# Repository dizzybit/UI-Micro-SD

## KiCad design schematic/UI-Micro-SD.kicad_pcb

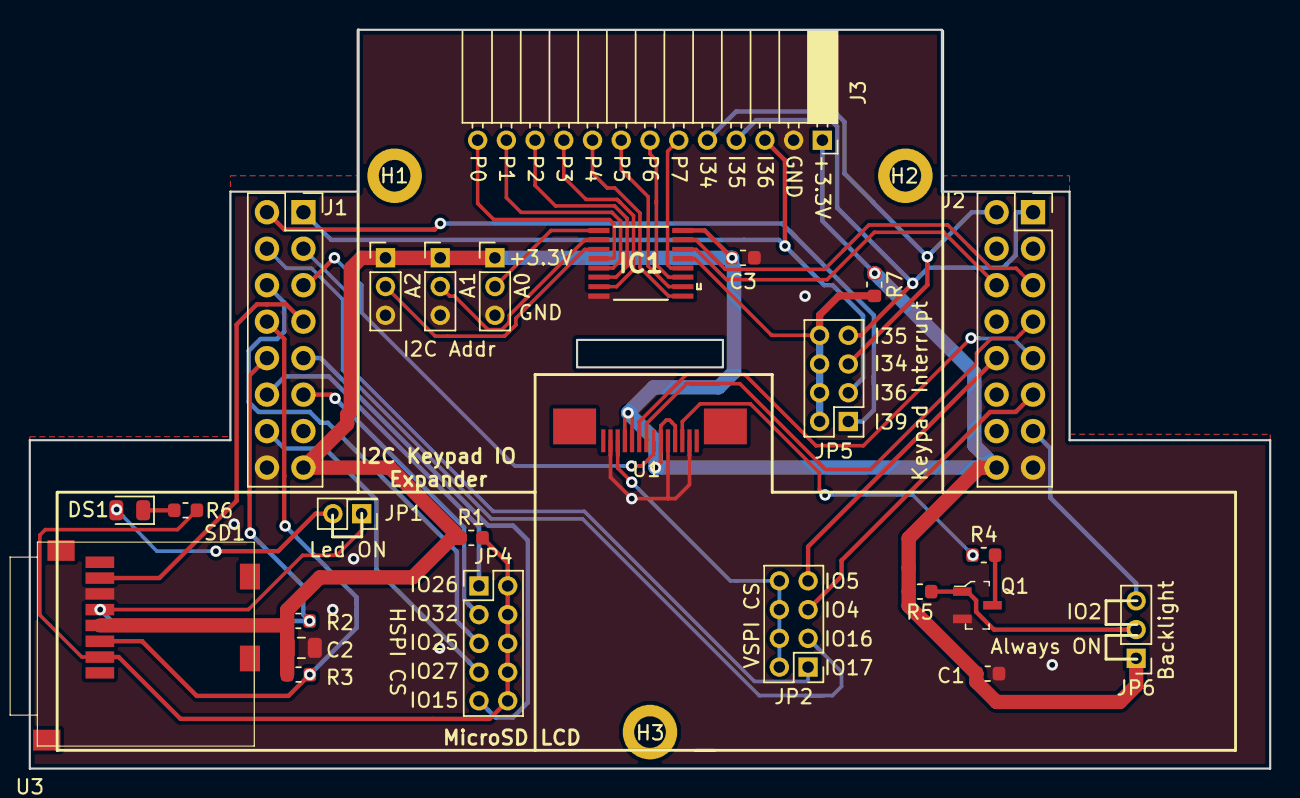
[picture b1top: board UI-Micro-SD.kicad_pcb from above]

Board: 2 copper layers, 86.4 x 51.4 mm, 31 parts (1 on the bottom side), 43 nets.

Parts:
C1: C0.1uF; C_0603_1608Metric
C2: C10uF/25V(10%); C_0805_2012Metric
C3: C0.1uF/50V(10%); C_0603_1608Metric
DS1: LED-BLUE; LED_0805_2012Metric
H1, H2, H3: MountingHole; MountingHole_2.2mm_M2_DIN965_Pad
IC1: TCA9554APWR; SOP65P640X120-16N
J1, J2: Conn_02x08_Odd_Even; PinSocket_2x08_P2.54mm_Vertical
J3: Conn_01x13; PinSocket_1x13_P2.00mm_Horizontal
J4, J5, J6: Conn_01x03; PinHeader_1x03_P2.00mm_Vertical
JP1: Conn_01x02; PinHeader_2x01_P2.00mm_Vertical
JP2, JP5: Conn_02x04_Odd_Even; PinHeader_2x04_P2.00mm_Vertical
JP4: Conn_02x05_Odd_Even; PinHeader_2x05_P2.00mm_Vertical
JP6: Conn_01x03; PinHeader_1x03_P2.00mm_Vertical
Q1: BSS138; SOT-23-3
R1, R2, R3, R7: R10K(1%); R_0603_1608Metric
R4: 4R7 Ohm; R_0603_1608Metric
R5: R10K; R_0603_1608Metric
R6: R330; R_0603_1608Metric
SD1: 47309-3351; DS1139-05
U1: SFV14R-3STBE1HLF
U2: DizzyBITLogo; DizzyBIT_silk_20
U3: DizzyBIT-Layout; DizzyBit-Din Rail Module

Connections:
+3V3: C1.1, C2.1, C3.1, IC1.16, J1.15, J2.16, J3.1, J4.1, J5.1, J6.1, JP6.1, R1.1, R2.1, R3.1, R5.2, R7.1, SD1.4, U1.4, U1.6, U1.10, U1.11
A0: IC1.1, J4.2
A1: IC1.2, J5.2
A2: IC1.3, J6.2
GND: C1.2, C2.2, C3.2, IC1.8, J1.16, J2.15, J3.2, J4.3, J5.3, J6.3, Q1.2, SD1.6, U1.2, U1.5, U1.13
HSPI_CLK: J1.10, JP1.1, R2.2, SD1.5
HSPI_CS: JP4.2, JP4.4, JP4.6, JP4.8, JP4.10, R1.2, R6.2, SD1.2
HSPI_MISO: J1.7, SD1.7
HSPI_MOSI: J1.8, R3.2, SD1.3
I2C_SCL: IC1.14, J2.6
I2C_SDA: IC1.15, J2.5
I34: J2.2, J3.5, JP5.5
I35: J2.1, J3.4, JP5.7
I36: J1.1, J3.3, JP5.3
I39: J1.2, JP5.1
INT: IC1.13, JP5.2, JP5.4, JP5.6, JP5.8, R7.2
IO2: J2.13, JP6.3
IO4: J2.11, JP2.5
IO5: J2.10, JP2.7
IO15: J1.9, JP4.9
IO16: J1.4, JP2.3
IO17: J1.3, JP2.1
IO25: J1.6, JP4.5
IO26: J1.12, JP4.1
IO27: J1.14, JP4.7
IO32: J1.11, JP4.3
IO33: J1.5, U1.7
LCD_BACKLIGHT: JP6.2, Q1.1, R5.1
LCD_LEDK: R4.1, U1.3
unnamed: DS1.1, R6.1
unnamed: DS1.2, JP1.2
unnamed: Q1.3, R4.2
P0: IC1.4, J3.13
P1: IC1.5, J3.12
P2: IC1.6, J3.11
P3: IC1.7, J3.10
P4: IC1.9, J3.9
P5: IC1.10, J3.8
P6: IC1.11, J3.7
P7: IC1.12, J3.6
VSPI_CLK: J2.9, U1.9
VSPI_CS: JP2.2, JP2.4, JP2.6, JP2.8, U1.12
VSPI_MOSI: J2.7, U1.8

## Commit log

2019-09-30 MicroSD, LCD 1.77 and UI keypad shield
2019-10-02 Changed Connector designators
2019-10-03 Working on positioning the components
    Changed the MicroSD footprint to match the connfly socket
2019-10-04 Designed tracks and silk labels
2019-10-04 Added 3D and Gerber files
2019-11-13 Fixed PN-s for display connector and IO expander
2019-12-20 Major Update. Changed pin configuration and board outline.
